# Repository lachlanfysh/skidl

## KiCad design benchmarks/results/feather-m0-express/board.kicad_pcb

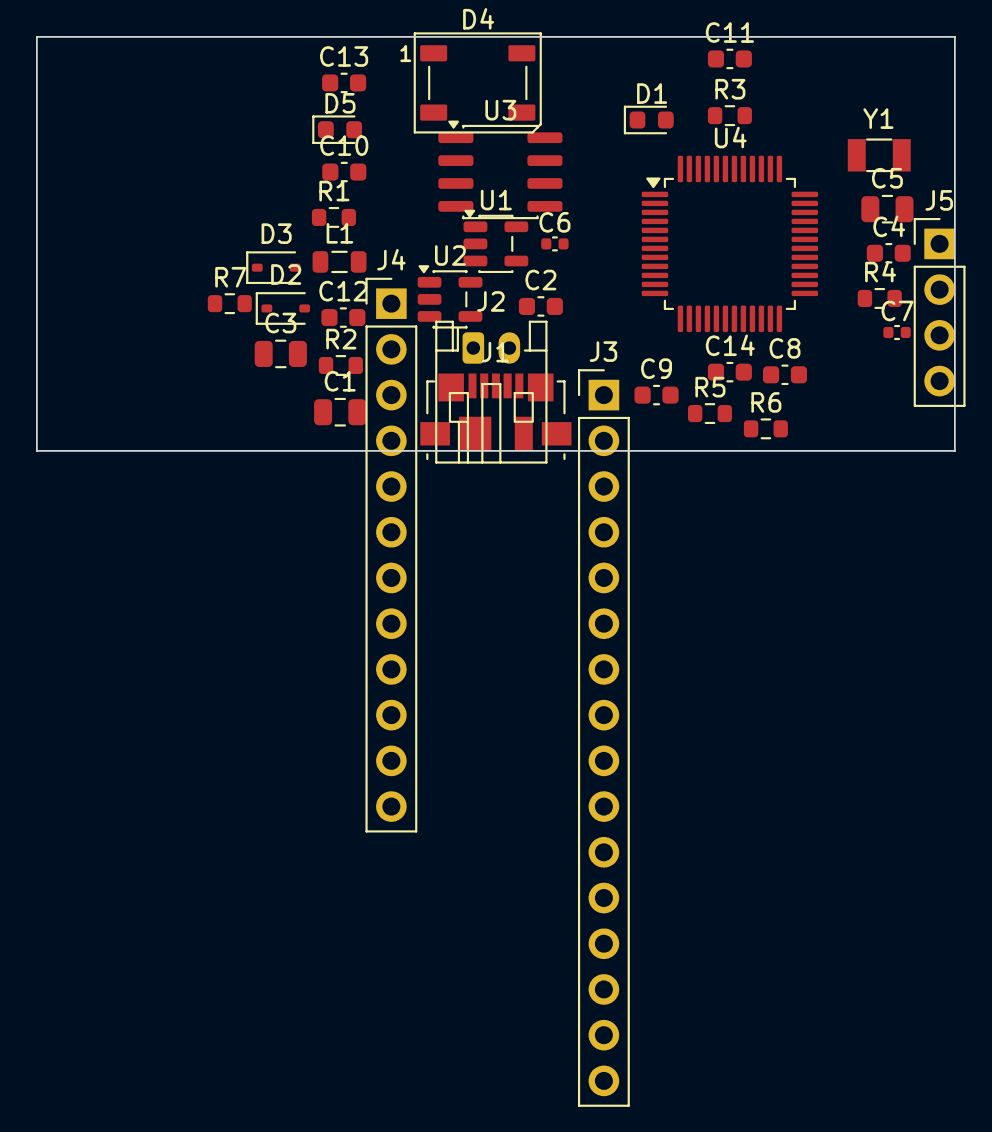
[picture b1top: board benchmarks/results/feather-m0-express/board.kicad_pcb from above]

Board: 2 copper layers, 51.0 x 23.0 mm, 37 parts (0 on the bottom side), 40 nets, no tracks yet.

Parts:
C1, C3, C5: 10uF; C_0805_2012Metric
C2, C4, C8, C9, C10, C12, C13, C14: 100nF; C_0603_1608Metric
C6, C7: 12pF; C_0402_1005Metric
C11: 1uF; C_0603_1608Metric
D1: Orange; LED_0603_1608Metric
D2, D3: MBR0520; D_SOD-323
D4: WS2812B; LED_WS2812B_PLCC4_5.0x5.0mm_P3.2mm
D5: Red; LED_0603_1608Metric
J1: USB_Micro_B; USB_Micro-B_Molex_47346-0001
J2: JST_PH_2; JST_PH_S2B-PH-K_1x02_P2.00mm_Horizontal
J3: Feather_Left; PinHeader_1x16_P2.54mm_Vertical
J4: Feather_Right; PinHeader_1x12_P2.54mm_Vertical
J5: SWD; PinHeader_1x04_P2.54mm_Vertical
L1: 600R@100MHz; L_0805_2012Metric
R1: 2K; R_0603_1608Metric
R2, R7: 1K; R_0603_1608Metric
R3, R4: 100K; R_0603_1608Metric
R5: 10K; R_0603_1608Metric
R6: SW_RST; R_0603_1608Metric
U1: MCP73831; SOT-23-5
U2: AP2112K-3.3; SOT-23-5
U3: GD25Q16C; SOIC-8_3.9x4.9mm_P1.27mm
U4: ATSAMD21G18A; TQFP-48_7x7mm_P0.5mm
Y1: 32.768kHz; Crystal_SMD_3215-2Pin_3.2x1.5mm

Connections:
+3V3: C4.1, C5.1, C9.1, C10.1, C12.1, C13.1, C14.1, D4.1, J3.2, J3.3, J5.1, R5.1, U2.5, U3.3, U3.7, U3.8, U4.6, U4.17, U4.36, U4.44
BAT_DIV: R3.2, R4.1, U4.12
FLASH_CS: U3.1, U4.22
GND: C1.2, C2.2, C3.2, C4.2, C5.2, C6.2, C7.2, C8.2, C9.2, C10.2, C11.2, C12.2, C13.2, C14.2, D4.3, D5.1, J1.5, J1.6, J2.2, J3.4, J5.4, R1.2, R4.2, R6.2, U1.2, U2.2, U3.4, U4.5, U4.18, U4.35, U4.42
HL_0: J3.5, U4.3
HL_1: J3.6, U4.4
HL_2: J3.7, U4.7
HL_3: J3.8, U4.8
HL_4: J3.9, U4.9
HL_5: J3.10, U4.10
HR_0: J4.4, R7.1, U4.26
HR_1: J4.5, U4.28
HR_2: J4.6, U4.25
HR_3: J4.7, U4.27
HR_4: J4.8, U4.29
HR_5: J4.9, U4.24
HR_6: J4.10, U4.23
HR_7: J3.14, U4.15
HR_8: J3.15, U4.16
MISO: J3.13, U3.2, U4.21
MOSI: J3.12, U3.5, U4.19
unnamed: R1.1, U1.5
unnamed: D1.2, R2.2
unnamed: D1.1, U1.1
unnamed: D5.2, R7.2
NEOPIXEL: D4.4, J3.16, U4.11
SCK: J3.11, U3.6, U4.20
SCL: J4.12, U4.32
SDA: J4.11, U4.31
SWCLK: J5.3, U4.45
SWDIO: J5.2, U4.46
USB_DM: J1.2, U4.33
USB_DP: J1.3, U4.34
VBAT: D3.2, J2.1, J4.1, R3.1, U1.3
VBUS: C1.1, C2.1, D2.2, J1.1, J4.3, L1.1, L1.2, R2.1, U1.4
VCC: C3.1, D2.1, D3.1, U2.1, U2.3
VDDCORE: C11.1, U4.43
XIN: C6.1, U4.1, Y1.1
XOUT: C7.1, U4.2, Y1.2
~RESET: C8.1, J3.1, R5.2, R6.1, U4.40

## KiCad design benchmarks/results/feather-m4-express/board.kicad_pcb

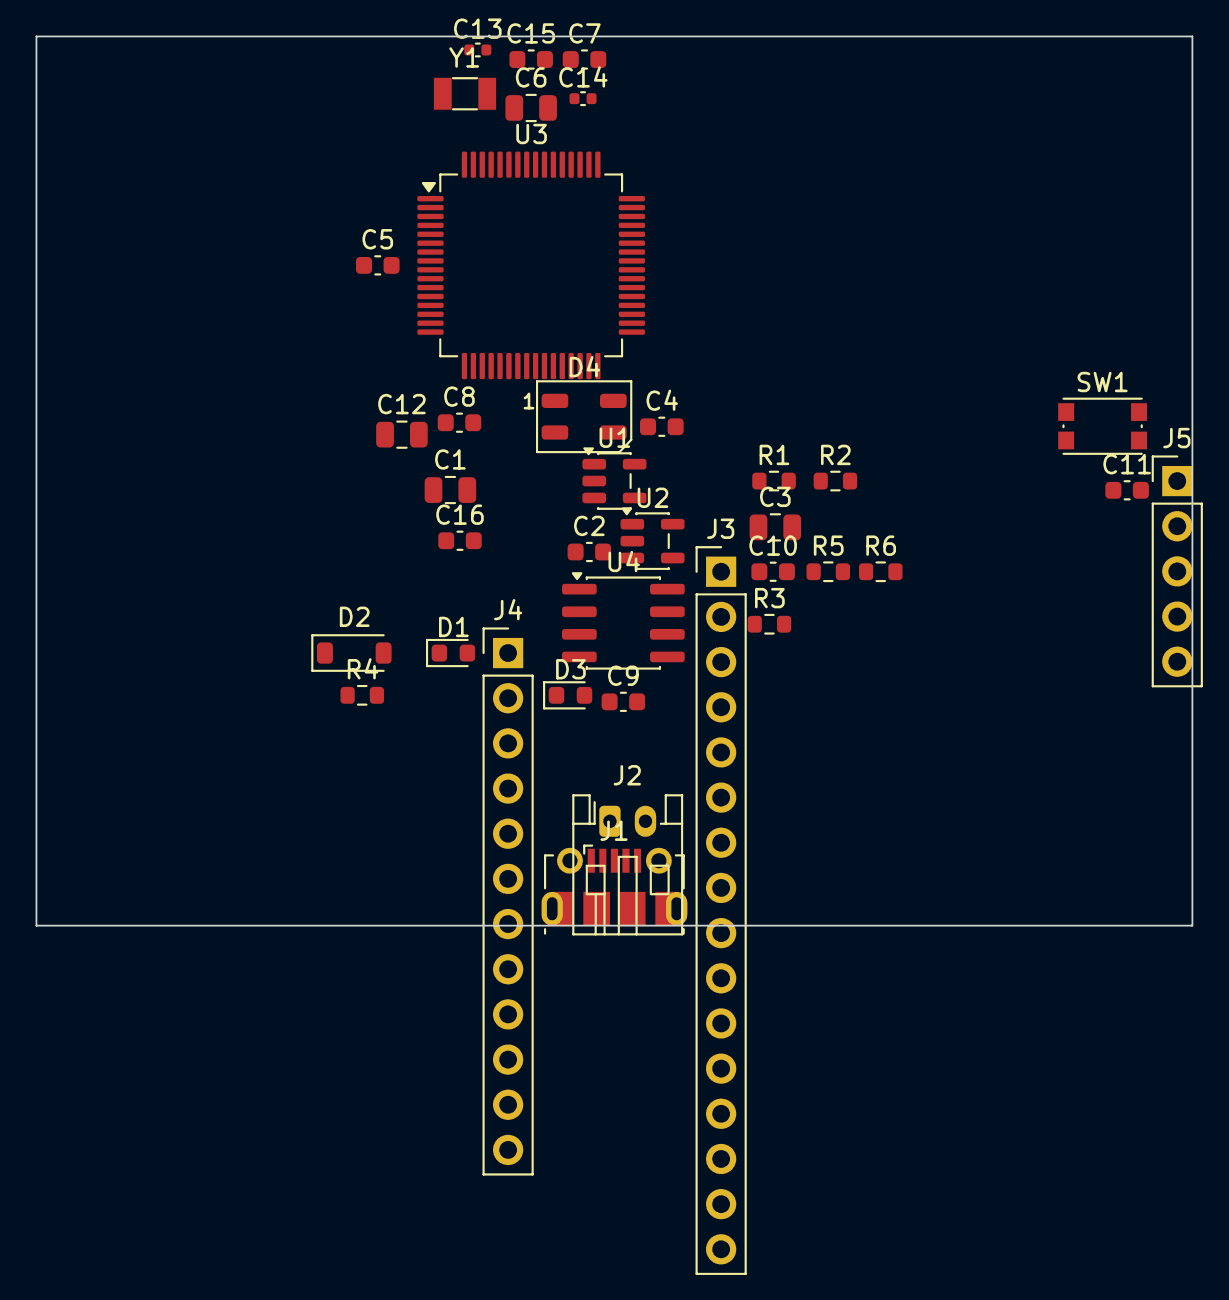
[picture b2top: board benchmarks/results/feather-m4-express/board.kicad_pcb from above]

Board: 2 copper layers, 65.0 x 50.0 mm, 37 parts (0 on the bottom side), 39 nets, no tracks yet.

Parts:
C1, C3, C6, C12: 10uF; C_0805_2012Metric
C2, C4, C5, C7, C8, C9, C10, C11, C15, C16: 100nF; C_0603_1608Metric
C13, C14: 12pF; C_0402_1005Metric
D1: Orange; LED_0603_1608Metric
D2: MBR120; D_SOD-123
D3: Red; LED_0603_1608Metric
D4: NeoPixel; LED_WS2812B-Mini_PLCC4_3.5x3.5mm
J1: USB_Micro-B; USB_Micro-B_Molex-105017-0001
J2: BATT; JST_PH_S2B-PH-K_1x02_P2.00mm_Horizontal
J3: HEADER_L; PinHeader_1x16_P2.54mm_Vertical
J4: HEADER_R; PinHeader_1x12_P2.54mm_Vertical
J5: SWD; PinHeader_1x05_P2.54mm_Vertical
R1: 2K; R_0603_1608Metric
R2, R4: 1K; R_0603_1608Metric
R3: 10K; R_0603_1608Metric
R5, R6: 4.7K; R_0603_1608Metric
SW1: RESET; SW_Push_1P1T_NO_CK_KMR2
U1: MCP73831; SOT-23-5
U2: AP2112K-3.3; SOT-23-5
U3: ATSAMD51J19A; TQFP-64_10x10mm_P0.5mm
U4: GD25Q16; SOIC-8_3.9x4.9mm_P1.27mm
Y1: 32.768kHz; Crystal_SMD_3215-2Pin_3.2x1.5mm

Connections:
+3V3: C5.1, C6.1, C8.1, C9.1, C10.1, C11.1, C12.1, C15.1, C16.1, D4.3, J3.2, J5.1, R3.1, R5.1, R6.1, U2.5, U3.8, U3.21, U3.34, U3.48, U3.56, U4.3, U4.7, U4.8
A0: J3.5, U3.3
A1: J3.6, U3.14
A2: J3.7, U3.11
A3: J3.8, U3.12
A4: J3.9, U3.13
A5: J3.10, U3.15
CHG_STAT: R2.1, U1.1
D4: J4.9, U3.31
D5: J3.13, U3.32
D6: J3.14, U3.37
D9: J3.15, J4.8, U3.38
D10: J3.16, J4.7, U3.41
D11: J4.6, U3.42
D12: J4.5, U3.4
D13: J4.4, R4.1, U3.35
FLASH_CS: U3.24, U4.1
GND: C1.2, C2.2, C3.2, C4.2, C5.2, C6.2, C7.2, C8.2, C9.2, C10.2, C11.2, C12.2, C13.2, C14.2, C15.2, C16.2, D3.1, D4.1, J1.5, J1.6, J2.2, J3.4, J5.2, R1.2, SW1.2, U1.2, U2.2, U3.7, U3.22, U3.33, U3.47, U3.54, U4.4
unnamed: R1.1, U1.5
unnamed: D1.1, R2.2
unnamed: D3.2, R4.2
NEOPIXEL: D4.2, U3.49
RESET_N: J3.1, J5.5, R3.2, SW1.1, U3.52
RX: J4.10, U3.40
SCL: J3.12, R6.2, U3.44
SDA: J3.11, R5.2, U3.43
SPI_MISO: J4.12, U3.18, U4.2
SPI_MOSI: U3.17, U4.5
SPI_SCK: U3.23, U4.6
SWDCLK: J5.4, U3.57
SWDIO: J5.3, U3.58
TX: J4.11, U3.39
USB_DM: J1.2, U3.45
USB_DP: J1.3, U3.46
VBAT: C3.1, C4.1, D2.1, J2.1, J4.1, U1.3, U2.1, U2.3
VBUS: C1.1, C2.1, D1.2, D2.2, J1.1, J4.3, U1.4
VDDCORE: C7.1, U3.53
XIN32: C13.1, U3.1, Y1.1
XOUT32: C14.1, U3.2, Y1.2

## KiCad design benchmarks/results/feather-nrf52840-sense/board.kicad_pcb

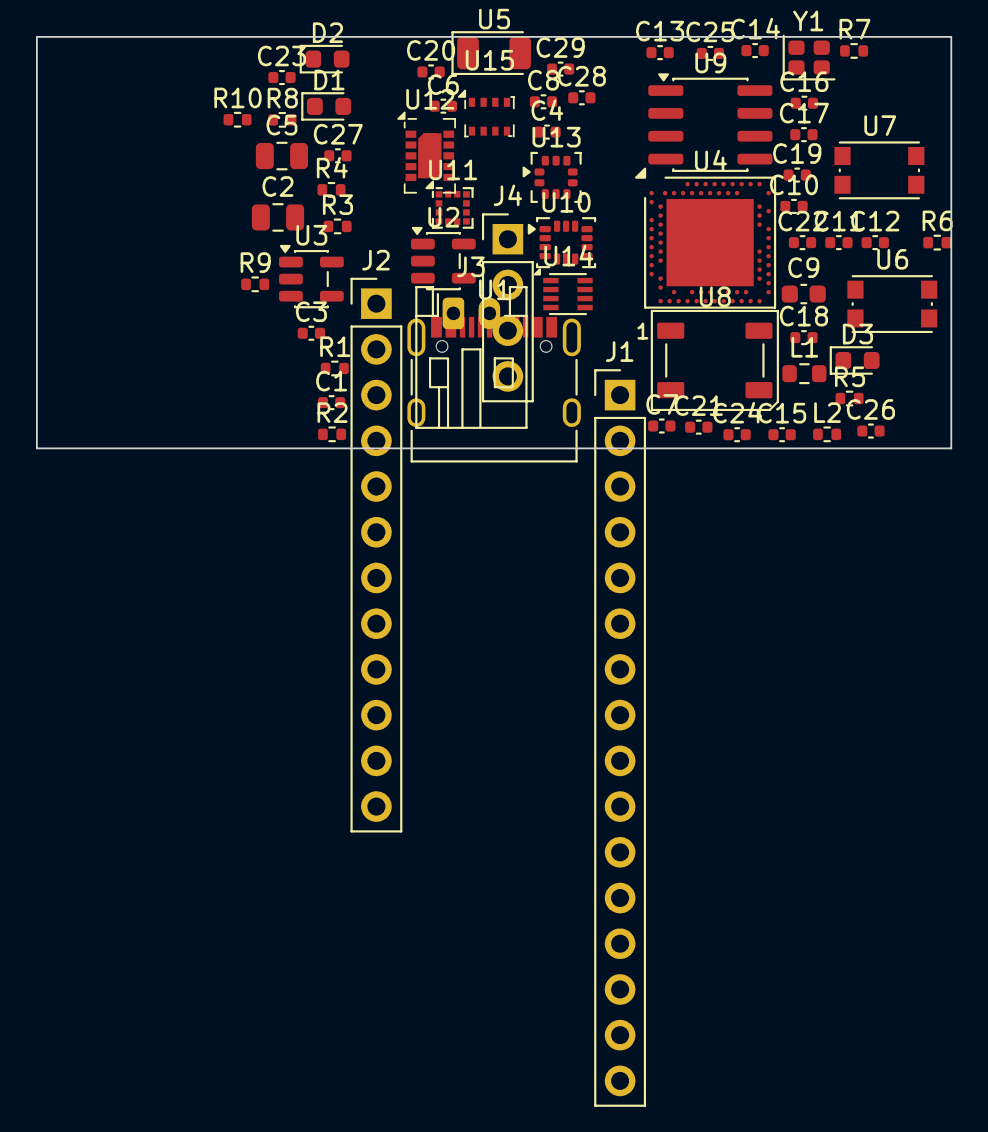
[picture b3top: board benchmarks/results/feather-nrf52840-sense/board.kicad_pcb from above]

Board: 2 copper layers, 50.8 x 22.9 mm, 64 parts (0 on the bottom side), 19 nets, no tracks yet.

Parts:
C1, C3, C4, C6, C7, C8, C10, C11, C12, C13, C14, C15, C20, C21, C22, C23, C24, C25, C27, C28, C29: 100nF; C_0402_1005Metric
C2, C5: 10uF; C_0805_2012Metric
C9: 4.7uF; C_0603_1608Metric
C16, C17: 12pF; C_0402_1005Metric
C18: 0.8pF; C_0402_1005Metric
C19: 1.0pF; C_0402_1005Metric
C26: 1uF; C_0402_1005Metric
D1: ORANGE; LED_0603_1608Metric
D2: RED; LED_0603_1608Metric
D3: BLUE; LED_0603_1608Metric
J1: Conn_01x16; PinHeader_1x16_P2.54mm_Vertical
J2: Conn_01x12; PinHeader_1x12_P2.54mm_Vertical
J3: Conn_01x02; JST_PH_S2B-PH-K_1x02_P2.00mm_Horizontal
J4: Conn_01x04; PinHeader_1x04_P2.54mm_Vertical
L1: 10uH; R_0603_1608Metric
L2: 3.3nH; R_0402_1005Metric
R1, R2: 5.1K; R_0402_1005Metric
R3: 2K; R_0402_1005Metric
R4, R6, R7: 1K; R_0402_1005Metric
R5: 10K; R_0402_1005Metric
R8, R9: 4.7K; R_0402_1005Metric
R10: 68R; R_0402_1005Metric
U1: USB_C_Receptacle; USB_C_Receptacle_XKB_U262-16XN-4BVC11
U2: MCP73831; SOT-23-5
U3: AP2112K-3.3; SOT-23-5
U4: nRF52840; Nordic_AQFN-73-1EP_7x7mm_P0.5mm
U5: ANT_2.4GHz; Johanson_2450AT18x100_2400-2500Mhz
U6: SW_RST; SW_Push_1P1T_NO_CK_KMR2
U7: SW_USR; SW_Push_1P1T_NO_CK_KMR2
U8: WS2812B; LED_WS2812B_PLCC4_5.0x5.0mm_P3.2mm
U9: GD25Q16; SOIC-8_3.9x4.9mm_P1.27mm
U10: LSM6DS33; LGA-14_3x2.5mm_P0.5mm_LayoutBorder3x4y
U11: LIS3MDL; LGA-12_2x2mm_P0.5mm
U12: APDS9960; AMS_LGA-10-1EP_2.7x4mm_P0.6mm
U13: MP34DT01; ST_HLGA-10_2.5x2.5mm_P0.6mm_LayoutBorder3x2y
U14: SHT30; DFN-8_2x2mm_P0.5mm
U15: BMP280; Bosch_LGA-8_2x2.5mm_P0.65mm_ClockwisePinNumbering
Y1: 32MHz; Crystal_SMD_2016-4Pin_2.0x1.6mm

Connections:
+3V3: C4.1, C5.1, C6.1, C7.1, C8.1, C9.1, C20.1, C21.1, C22.1, C24.1, C25.1, C26.1, C27.1, C28.1, C29.1, J1.2, J4.1, L1.2, R5.1, R8.1, R9.1, U3.5, U8.1, U9.8, U10.5, U10.8, U10.12, U11.4, U11.5, U11.10, U12.4, U12.5, U12.10, U13.5, U14.5, U14.6, U15.2, U15.6, U15.8
ANT_RF: C19.1, L2.2, U5.1
GND: C1.2, C2.2, C3.2, C4.2, C5.2, C6.2, C7.2, C8.2, C9.2, C10.2, C11.2, C12.2, C13.2, C14.2, C15.2, C16.2, C17.2, C18.2, C19.2, C20.2, C21.2, C22.2, C23.2, C24.2, C25.2, C26.2, C27.2, C28.2, C29.2, D1.2, D2.2, D3.2, J1.4, J3.2, J4.4, R1.2, R2.2, R3.2, R10.2, U2.2, U3.2, U4.EP, U5.2, U6.2, U7.2, U8.3, U9.4, U10.1, U10.6, U10.7, U11.2, U11.9, U11.11, U11.12, U12.2, U12.6, U12.11, U13.2, U13.4, U13.9, U13.10, U14.2, U14.8, U15.1, U15.5, U15.7
unnamed: R3.1, U2.5
unnamed: R4.1, U2.1
unnamed: D1.1, R4.2
unnamed: C16.1, Y1.1
unnamed: C17.1, Y1.2
unnamed: C18.1, L2.1
unnamed: R5.2, U6.1
unnamed: D2.1, R6.2
unnamed: D3.1, R7.2
unnamed: U4.P23, U9.1
unnamed: C23.1, U11.3
unnamed: R10.1, U12.3
SCL: J2.12, R9.2, U10.13, U11.1, U12.7, U14.4, U15.4
SDA: J2.11, R8.2, U10.14, U11.8, U12.1, U14.1, U15.3
VBAT: C2.1, C3.1, J2.1, J3.1, U2.3, U3.1, U3.3
VBUS: C1.1, J2.3, U2.4

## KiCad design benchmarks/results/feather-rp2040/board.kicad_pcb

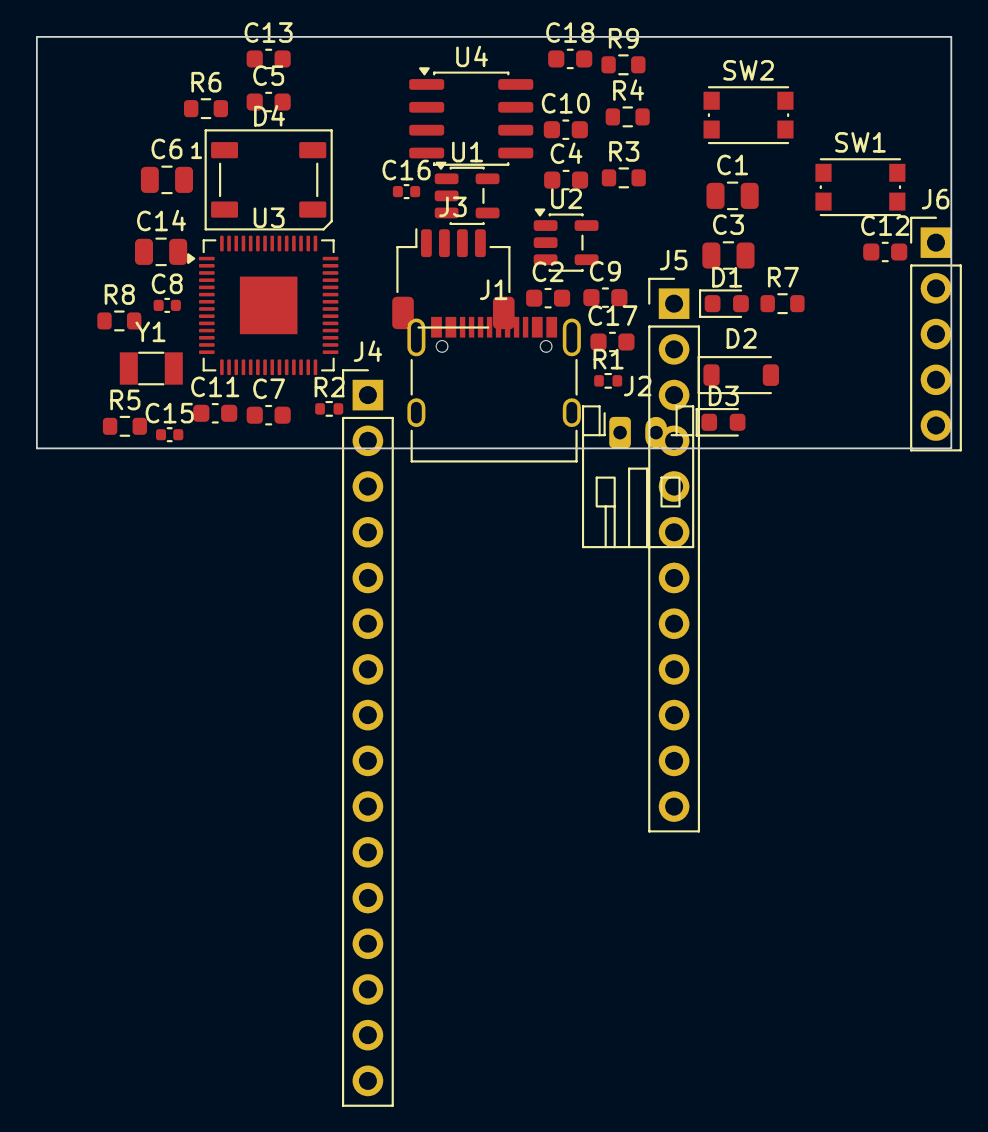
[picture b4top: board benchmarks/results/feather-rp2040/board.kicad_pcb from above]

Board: 2 copper layers, 50.8 x 22.9 mm, 44 parts (0 on the bottom side), 45 nets, no tracks yet.

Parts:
C1, C3, C6, C14: 10uF; C_0805_2012Metric
C2, C4, C5, C7, C9, C10, C11, C12, C13, C17, C18: 100nF; C_0603_1608Metric
C8: 1uF; C_0402_1005Metric
C15, C16: 15pF; C_0402_1005Metric
D1: Orange; LED_0603_1608Metric
D2: MBR120; D_SOD-123
D3: Red; LED_0603_1608Metric
D4: NeoPixel; LED_WS2812B_PLCC4_5.0x5.0mm_P3.2mm
J1: USB-C; USB_C_Receptacle_XKB_U262-16XN-4BVC11
J2: BATT; JST_PH_S2B-PH-K_1x02_P2.00mm_Horizontal
J3: STEMMA_QT; JST_SH_SM04B-SRSS-TB_1x04-1MP_P1.00mm_Horizontal
J4: HEADER_L; PinHeader_1x16_P2.54mm_Vertical
J5: HEADER_R; PinHeader_1x12_P2.54mm_Vertical
J6: SWD; PinHeader_1x05_P2.54mm_Vertical
R1, R2: 5.1K; R_0402_1005Metric
R3: 2K; R_0603_1608Metric
R4, R7: 1K; R_0603_1608Metric
R5, R6: 10K; R_0603_1608Metric
R8, R9: 4.7K; R_0603_1608Metric
SW1: RESET; SW_Push_1P1T_NO_CK_KMR2
SW2: BOOTSEL; SW_Push_1P1T_NO_CK_KMR2
U1: MCP73831; SOT-23-5
U2: AP2112K-3.3; SOT-23-5
U3: RP2040; QFN-56-1EP_7x7mm_P0.4mm_EP3.2x3.2mm
U4: GD25Q64; SOIC-8_3.9x4.9mm_P1.27mm
Y1: 12MHz; Crystal_SMD_3215-2Pin_3.2x1.5mm

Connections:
+3V3: C5.1, C6.1, C9.1, C10.1, C11.1, C12.1, C13.1, C14.1, C17.1, C18.1, D4.3, J3.2, J4.2, J6.1, R5.1, R6.1, R8.1, R9.1, U2.5, U3.1, U3.10, U3.22, U3.33, U3.42, U3.43, U3.44, U3.48, U3.49, U4.8
A0: J4.5, U3.38
A1: J4.6, U3.39
A2: J4.7, U3.40
A3: J4.8, U3.41
BOOTSEL: R6.2, SW2.1
CHG_STAT: R4.1, U1.1
D4: J5.9, U3.6
D5: J4.13, U3.7
D6: J4.14, U3.8
D9: J4.15, J5.8, U3.9
D10: J4.16, J5.7, U3.11
D11: J5.6, U3.12
D12: J5.5, U3.13
D13: J5.4, R7.1, U3.14
D24: J4.9, U3.36
D25: J4.10, U3.37
DVDD: C7.1, C8.1, U3.23, U3.45, U3.50
GND: C1.2, C2.2, C3.2, C4.2, C5.2, C6.2, C7.2, C8.2, C9.2, C10.2, C11.2, C12.2, C13.2, C14.2, C15.2, C16.2, C17.2, C18.2, D3.1, D4.1, J1.A1, J1.A12, J1.B1, J1.B12, J1.S1, J2.2, J3.1, J4.4, J6.2, R1.2, R2.2, R3.2, SW1.2, SW2.2, U1.2, U2.2, U3.19, U3.57, U4.4
unnamed: J1.A5, R1.1
unnamed: J1.B5, R2.1
unnamed: R3.1, U1.5
unnamed: D1.1, R4.2
unnamed: D3.2, R7.2
NEOPIXEL: D4.2, U3.27
QSPI_SCLK: U3.52, U4.6
QSPI_SD0: U3.53, U4.5
QSPI_SD1: U3.55, U4.2
QSPI_SD2: U3.54, U4.3
QSPI_SD3: U3.51, U4.7
QSPI_SS: U3.56, U4.1
RESET_N: J4.1, J6.5, R5.2, SW1.1, U3.26
RX: J5.10, U3.3
SCL: J3.4, J4.12, R9.2, U3.5
SDA: J3.3, J4.11, R8.2, U3.4
SPI_MISO: J5.12, U3.31
SWDCLK: J6.4, U3.24
SWDIO: J6.3, U3.25
TX: J5.11, U3.2
USB_DM: J1.A7, J1.B7, U3.46
USB_DP: J1.A6, J1.B6, U3.47
VBAT: C3.1, C4.1, D2.1, J2.1, J5.1, U1.3, U2.1, U2.3
VBUS: C1.1, C2.1, D1.2, D2.2, J1.A4, J1.A9, J1.B4, J1.B9, J5.3, U1.4
XIN: C15.1, U3.20, Y1.1
XOUT: C16.1, U3.21, Y1.2

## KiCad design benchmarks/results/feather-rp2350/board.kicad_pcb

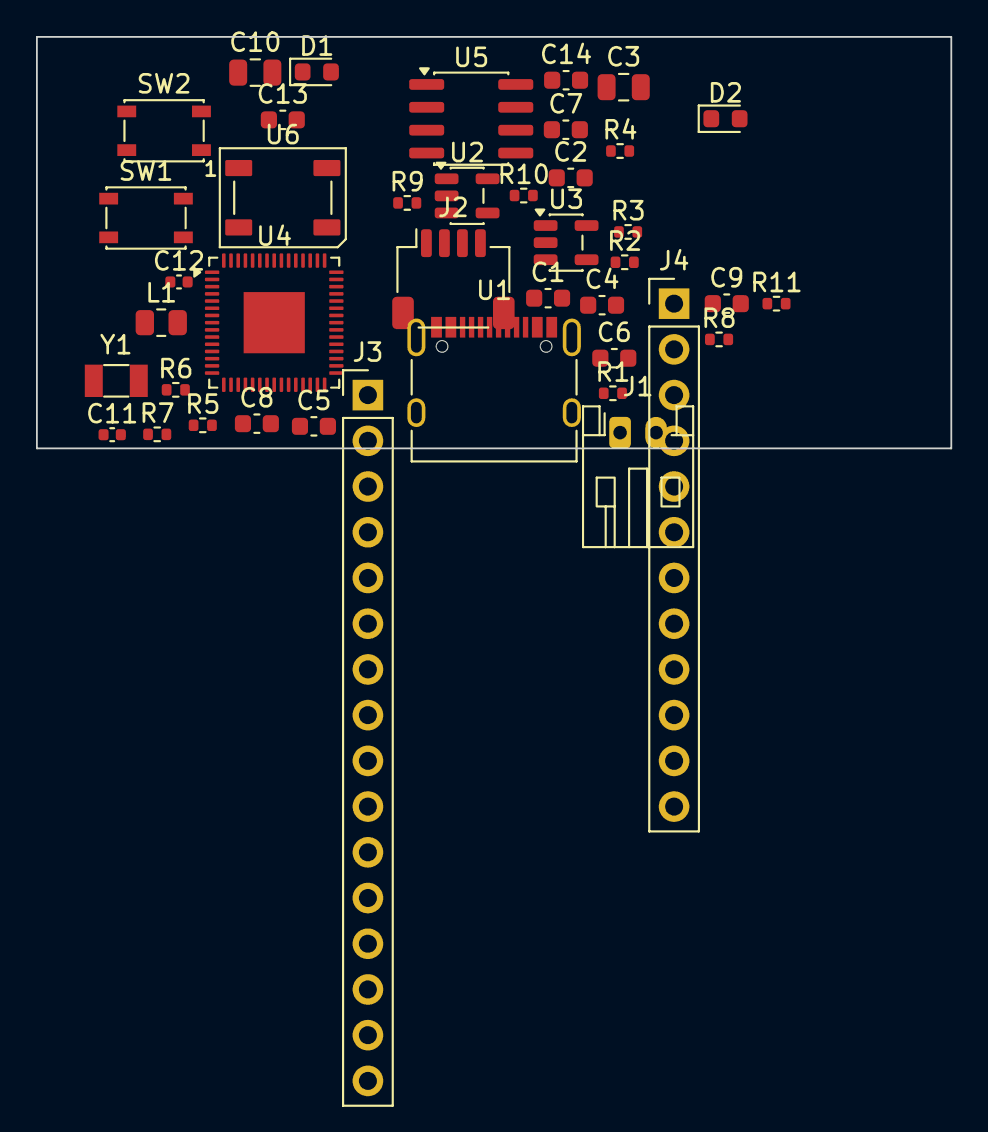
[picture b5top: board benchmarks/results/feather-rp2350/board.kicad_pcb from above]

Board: 2 copper layers, 50.8 x 22.9 mm, 41 parts (0 on the bottom side), 46 nets, no tracks yet.

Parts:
C1, C2, C4, C5, C6, C7, C8, C9, C13, C14: 100nF; C_0603_1608Metric
C3, C10: 10uF; C_0805_2012Metric
C11, C12: 20pF; C_0402_1005Metric
D1: ORANGE; LED_0603_1608Metric
D2: RED; LED_0603_1608Metric
J1: Conn_01x02; JST_PH_S2B-PH-K_1x02_P2.00mm_Horizontal
J2: Conn_01x04; JST_SH_SM04B-SRSS-TB_1x04-1MP_P1.00mm_Horizontal
J3: Conn_01x16; PinHeader_1x16_P2.54mm_Vertical
J4: Conn_01x12; PinHeader_1x12_P2.54mm_Vertical
L1: 3.3uH; R_0805_2012Metric
R1, R2: 5.1K; R_0402_1005Metric
R3: 2K; R_0402_1005Metric
R4: 1K; R_0402_1005Metric
R5: 100K; R_0402_1005Metric
R6: 220K; R_0402_1005Metric
R7, R10: 10K; R_0402_1005Metric
R8, R9: 4.7K; R_0402_1005Metric
R11: 330R; R_0402_1005Metric
SW1, SW2: SW_Push; SW_SPST_PTS810
U1: USB_C_16P; USB_C_Receptacle_XKB_U262-16XN-4BVC11
U2: AP2112K-3.3; SOT-23-5
U3: MCP73831; SOT-23-5
U4: RP2350A; QFN-60-1EP_7x7mm_P0.4mm_EP3.4x3.4mm
U5: W25Q64JV; SOIC-8_3.9x4.9mm_P1.27mm
U6: WS2812B; LED_WS2812B_PLCC4_5.0x5.0mm_P3.2mm
Y1: 12MHz; Crystal_SMD_3215-2Pin_3.2x1.5mm

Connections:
+3V3: C2.1, C3.1, C6.1, C7.1, C8.1, C9.1, C10.1, C13.1, C14.1, J2.2, J3.2, J4.1, L1.2, R5.1, R7.1, R8.1, R9.1, R10.1, U2.5, U4.1, U4.6, U4.11, U4.20, U4.23, U4.30, U4.38, U4.39, U4.44, U4.45, U4.46, U4.49, U4.53, U4.54, U5.8, U6.1
BOOTSEL: R10.2, SW2.1
CHG_STAT: R4.1, U3.1
GND: C1.2, C2.2, C3.2, C4.2, C5.2, C6.2, C7.2, C8.2, C9.2, C10.2, C11.2, C12.2, C13.2, C14.2, D1.2, D2.2, J1.2, J2.1, J3.16, J4.3, R1.2, R2.2, R3.2, R6.2, SW1.2, SW2.2, U1.A1, U1.A12, U1.B1, U1.B12, U1.S1, U2.2, U3.2, U4.47, U4.61, U5.4, U6.3
GPIO0: J3.15, U4.2
GPIO1: J3.14, U4.3
GPIO4: J4.12, U4.7
GPIO8: J3.10, U4.12
GPIO9: J3.9, U4.13
GPIO10: J3.8, U4.14
GPIO11: J3.7, U4.15
GPIO12: J3.6, U4.16
GPIO13: J3.5, U4.17
GPIO14: J3.4, U4.18
GPIO21: J4.9, U4.33
GPIO22: J3.13, U4.34
GPIO23: J3.12, U4.35
GPIO24: J3.11, U4.36
GPIO25: J4.8, R11.1, U4.37
GPIO26: J4.4, U4.40
GPIO27: J4.5, U4.41
GPIO28: J4.6, U4.42
GPIO29: J4.2, J4.7, U4.43
unnamed: R1.1, U1.A5
unnamed: R2.1, U1.B5
unnamed: R3.1, U3.5
unnamed: D1.1, R4.2
unnamed: D2.1, R11.2
NEOPIXEL: U4.27, U6.4
QSPI_CLK: U4.56, U5.6
QSPI_CS: U4.60, U5.1
QSPI_D0: U4.57, U5.5
QSPI_D1: U4.59, U5.2
QSPI_D2: U4.58, U5.3
QSPI_D3: U4.55, U5.7
RUN1: R7.2, U4.26
SCL: J2.4, J4.10, R9.2, U4.5
SDA: J2.3, J4.11, R8.2, U4.4
USB_DM: U1.A7, U1.B7, U4.51
USB_DP: U1.A6, U1.B6, U4.52
VBAT: C5.1, J1.1, J3.1, U3.3
VBUS: C1.1, C4.1, J3.3, U1.A4, U1.A9, U1.B4, U1.B9, U2.1, U2.3, U3.4
VREG_FB: R5.2, R6.1, U4.50
VREG_LX: L1.1, U4.48
XIN: C11.1, U4.21, Y1.1
XOUT: C12.1, U4.22, Y1.2

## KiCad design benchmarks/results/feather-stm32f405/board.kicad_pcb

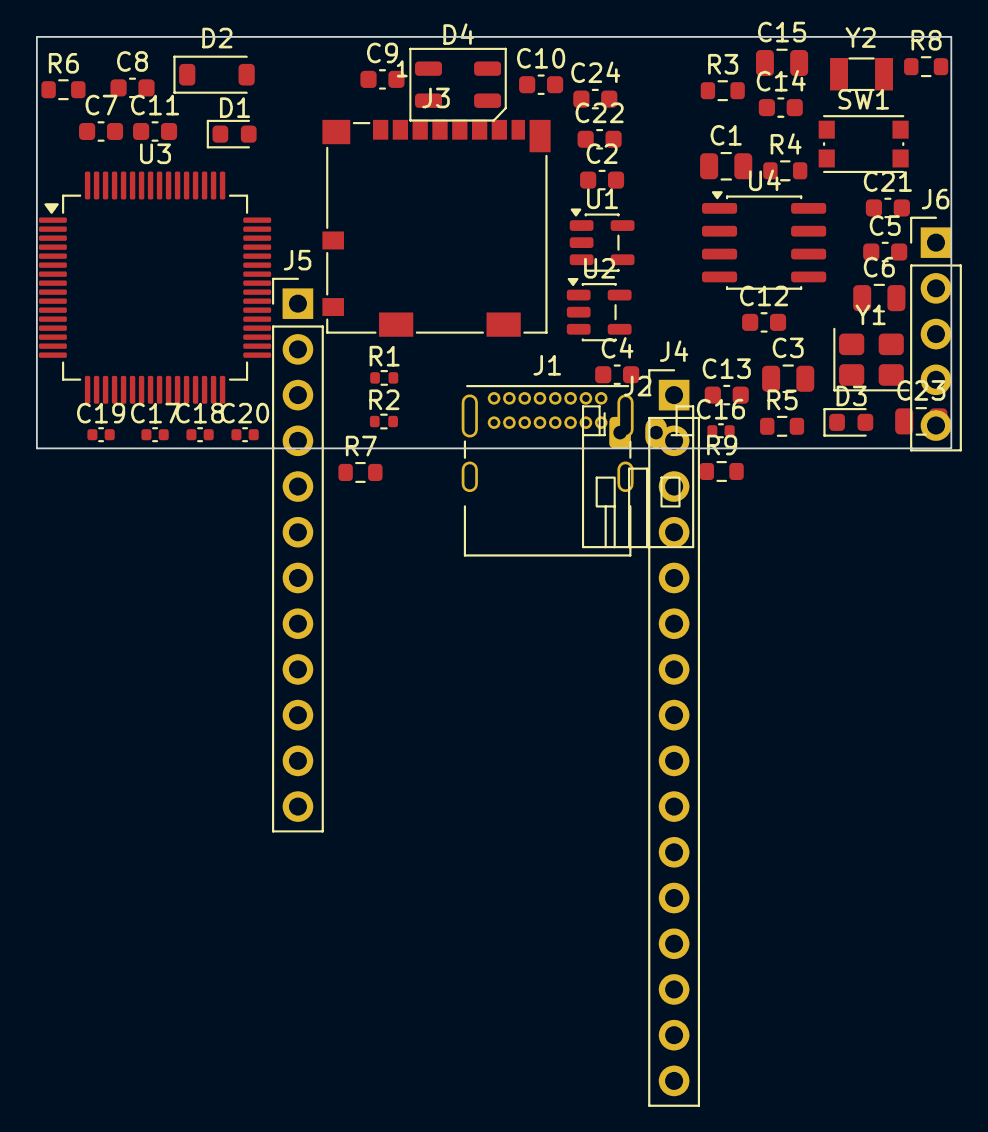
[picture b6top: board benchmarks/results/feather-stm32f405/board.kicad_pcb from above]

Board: 2 copper layers, 50.8 x 22.9 mm, 50 parts (0 on the bottom side), 49 nets, no tracks yet.

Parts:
C1, C3, C6, C15, C23: 10uF; C_0805_2012Metric
C2, C4, C5, C9, C10, C11, C12, C13, C21, C22, C24: 100nF; C_0603_1608Metric
C7, C8: 2.2uF; C_0603_1608Metric
C14: 1uF; C_0603_1608Metric
C16: 100nF; C_0402_1005Metric
C17, C18: 20pF; C_0402_1005Metric
C19, C20: 6.8pF; C_0402_1005Metric
D1: Orange; LED_0603_1608Metric
D2: MBR120; D_SOD-123
D3: Red; LED_0603_1608Metric
D4: NeoPixel; LED_WS2812B-Mini_PLCC4_3.5x3.5mm
J1: USB-C; USB_C_Receptacle_GCT_USB4085
J2: BATT; JST_PH_S2B-PH-K_1x02_P2.00mm_Horizontal
J3: MicroSD; microSD_HC_Molex_104031-0811
J4: HEADER_L; PinHeader_1x16_P2.54mm_Vertical
J5: HEADER_R; PinHeader_1x12_P2.54mm_Vertical
J6: SWD; PinHeader_1x05_P2.54mm_Vertical
R1, R2: 5.1K; R_0402_1005Metric
R3: 2K; R_0603_1608Metric
R4, R7: 1K; R_0603_1608Metric
R5, R6: 10K; R_0603_1608Metric
R8, R9: 4.7K; R_0603_1608Metric
SW1: RESET; SW_Push_1P1T_NO_CK_KMR2
U1: MCP73831; SOT-23-5
U2: AP2112K-3.3; SOT-23-5
U3: STM32F405RGT6; LQFP-64_10x10mm_P0.5mm
U4: GD25Q16; SOIC-8_3.9x4.9mm_P1.27mm
Y1: 8MHz; Crystal_SMD_3225-4Pin_3.2x2.5mm
Y2: 32.768kHz; Crystal_SMD_3215-2Pin_3.2x1.5mm

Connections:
+3V3: C5.1, C6.1, C9.1, C10.1, C11.1, C12.1, C13.1, C14.1, C15.1, C21.1, C22.1, C23.1, C24.1, D4.3, J3.4, J4.2, J6.1, R5.1, R8.1, R9.1, U2.5, U3.1, U3.13, U3.19, U3.32, U3.48, U3.64, U4.3, U4.7, U4.8
A0: J4.5, U3.14
A1: J4.6, U3.15
A2: J4.7, U3.16
A3: J4.8, U3.17
A4: J4.9, U3.20
A5: J4.10, U3.21
BOOT0: R6.1, U3.60
CC1: J1.A5, R1.1
CC2: J1.B5, R2.1
CHG_STAT: R4.1, U1.1
D4: J5.9, U3.27
D5: J4.13, U3.38
D6: J4.14, U3.37
D9: J4.15, J5.8, U3.61
D10: J4.16, J5.7, U3.62
D11: J5.6, U3.11
D12: J5.5, U3.10
D13: J5.4, R7.1, U3.9
FLASH_CS: U3.50, U4.1
GND: C1.2, C2.2, C3.2, C4.2, C5.2, C6.2, C7.2, C8.2, C9.2, C10.2, C11.2, C12.2, C13.2, C14.2, C15.2, C16.2, C17.2, C18.2, C19.2, C20.2, C21.2, C22.2, C23.2, C24.2, D3.1, D4.1, J1.A1, J1.A12, J1.B1, J1.B12, J1.S1, J2.2, J3.6, J3.9, J4.4, J6.2, R1.2, R2.2, R3.2, R6.2, SW1.2, U1.2, U2.2, U3.12, U3.18, U3.63, U4.4
HSE_IN: C17.1, U3.5, Y1.1
HSE_OUT: C18.1, U3.6, Y1.2
LSE_IN: C19.1, U3.3, Y2.1
LSE_OUT: C20.1, U3.4, Y2.2
unnamed: R3.1, U1.5
unnamed: D1.1, R4.2
unnamed: D3.2, R7.2
NEOPIXEL: D4.2, U3.8
RESET_N: C16.1, J4.1, J6.5, R5.2, SW1.1, U3.7
RX: J5.10, U3.30
SCL: J4.12, R9.2, U3.58
SDA: J4.11, R8.2, U3.59
SD_CS: J3.2, U3.33
SD_MISO: J3.7, U3.35
SD_MOSI: J3.3, U3.36
SD_SCK: J3.5, U3.34
SPI_MISO: J5.12, U3.56, U4.2
SPI_MOSI: U3.57, U4.5
SPI_SCK: U3.55, U4.6
SWDCLK: J6.4, U3.49
SWDIO: J6.3, U3.46
TX: J5.11, U3.29
USB_DM: J1.A7, J1.B7, U3.44
USB_DP: J1.A6, J1.B6, U3.45
VBAT: C3.1, C4.1, D2.1, J2.1, J5.1, U1.3, U2.1, U2.3
VBUS: C1.1, C2.1, D1.2, D2.2, J1.A4, J1.A9, J1.B4, J1.B9, J5.3, U1.4
VCAP1: C7.1, U3.31
VCAP2: C8.1, U3.47

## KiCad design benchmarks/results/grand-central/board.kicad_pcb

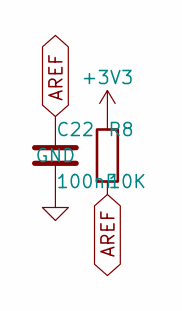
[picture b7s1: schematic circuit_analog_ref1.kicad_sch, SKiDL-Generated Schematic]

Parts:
C22: 100nF; C_0603_1608Metric
R8: 10K; R_0603_1608Metric

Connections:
+3V3: R8.1; also elsewhere on the board
AREF: C22.1, R8.2; also elsewhere on the board
GND: C22.2; also elsewhere on the board

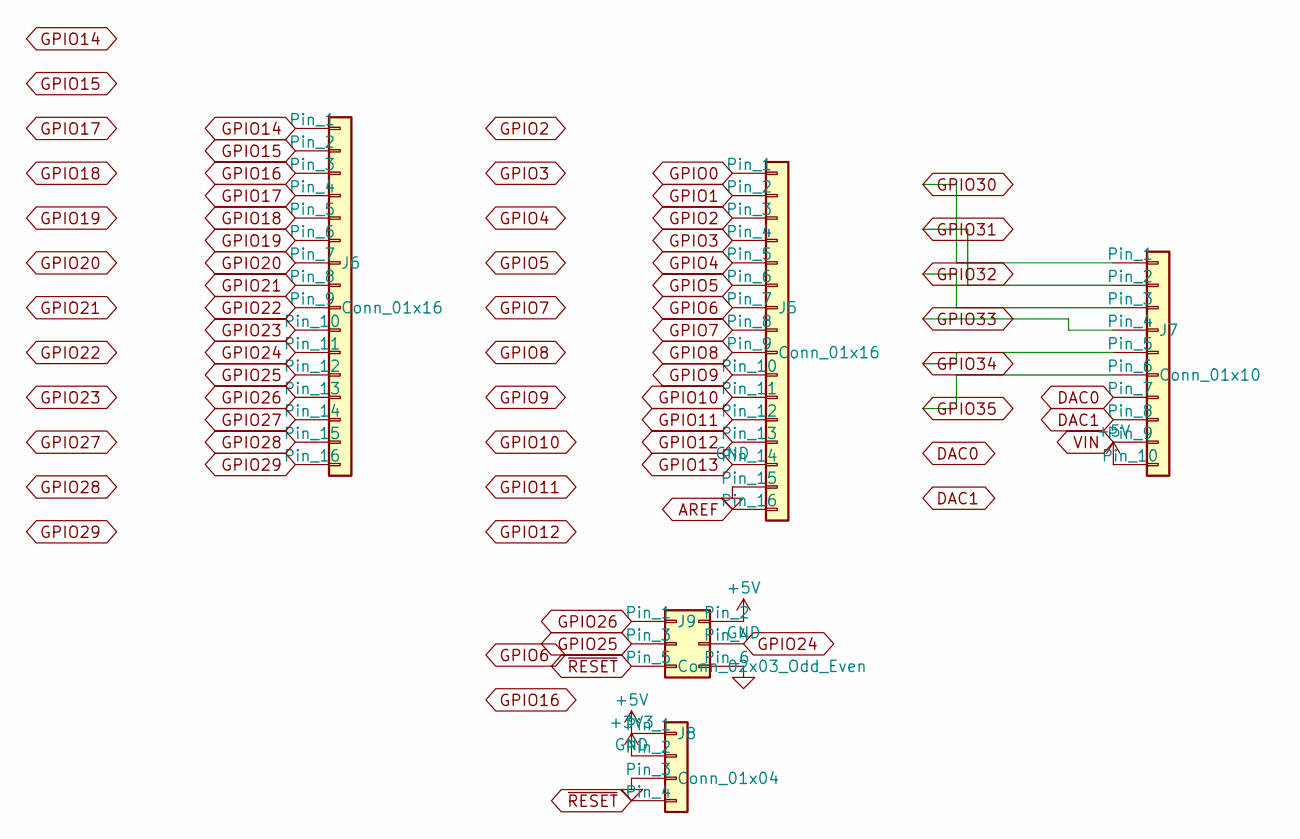
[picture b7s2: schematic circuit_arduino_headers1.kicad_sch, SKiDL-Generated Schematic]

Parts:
J5, J6: Conn_01x16; PinHeader_1x16_P2.54mm_Vertical
J7: Conn_01x10; PinHeader_1x10_P2.54mm_Vertical
J8: Conn_01x04; PinHeader_1x04_P2.54mm_Vertical
J9: Conn_02x03_Odd_Even; PinHeader_2x03_P2.54mm_Vertical

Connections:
+3V3: J8.2; also elsewhere on the board
+5V: J7.10, J8.1, J9.2; also elsewhere on the board
AREF: J5.16; also elsewhere on the board
DAC0: J7.7; also elsewhere on the board
DAC1: J7.8; also elsewhere on the board
GND: J5.15, J8.3, J9.6; also elsewhere on the board
GPIO0: J5.1; also elsewhere on the board
GPIO1: J5.2; also elsewhere on the board
GPIO2: J5.3; also elsewhere on the board
GPIO3: J5.4; also elsewhere on the board
GPIO4: J5.5; also elsewhere on the board
GPIO5: J5.6; also elsewhere on the board
GPIO6: J5.7; also elsewhere on the board
GPIO7: J5.8; also elsewhere on the board
GPIO8: J5.9; also elsewhere on the board
GPIO9: J5.10; also elsewhere on the board
GPIO10: J5.11; also elsewhere on the board
GPIO11: J5.12; also elsewhere on the board
GPIO12: J5.13; also elsewhere on the board
GPIO13: J5.14; also elsewhere on the board
GPIO14: J6.1; also elsewhere on the board
GPIO15: J6.2; also elsewhere on the board
GPIO16: J6.3; also elsewhere on the board
GPIO17: J6.4; also elsewhere on the board
GPIO18: J6.5; also elsewhere on the board
GPIO19: J6.6; also elsewhere on the board
GPIO20: J6.7; also elsewhere on the board
GPIO21: J6.8; also elsewhere on the board
GPIO22: J6.9; also elsewhere on the board
GPIO23: J6.10; also elsewhere on the board
GPIO24: J6.11, J9.4; also elsewhere on the board
GPIO25: J6.12, J9.3; also elsewhere on the board
GPIO26: J6.13, J9.1; also elsewhere on the board
GPIO27: J6.14; also elsewhere on the board
GPIO28: J6.15; also elsewhere on the board
GPIO29: J6.16; also elsewhere on the board
GPIO30: J7.1
GPIO31: J7.2
GPIO32: J7.3
GPIO33: J7.4
GPIO34: J7.5
GPIO35: J7.6
VIN: J7.9; also elsewhere on the board
~RESET: J8.4, J9.5; also elsewhere on the board

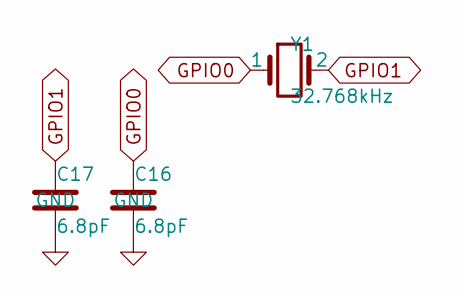
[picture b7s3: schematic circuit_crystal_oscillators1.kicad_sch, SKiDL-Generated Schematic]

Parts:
C16, C17: 6.8pF; C_0603_1608Metric
Y1: 32.768kHz; Crystal_SMD_2012-2Pin_2.0x1.2mm

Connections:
GND: C16.2, C17.2; also elsewhere on the board
GPIO0: C16.1, Y1.1; also elsewhere on the board
GPIO1: C17.1, Y1.2; also elsewhere on the board

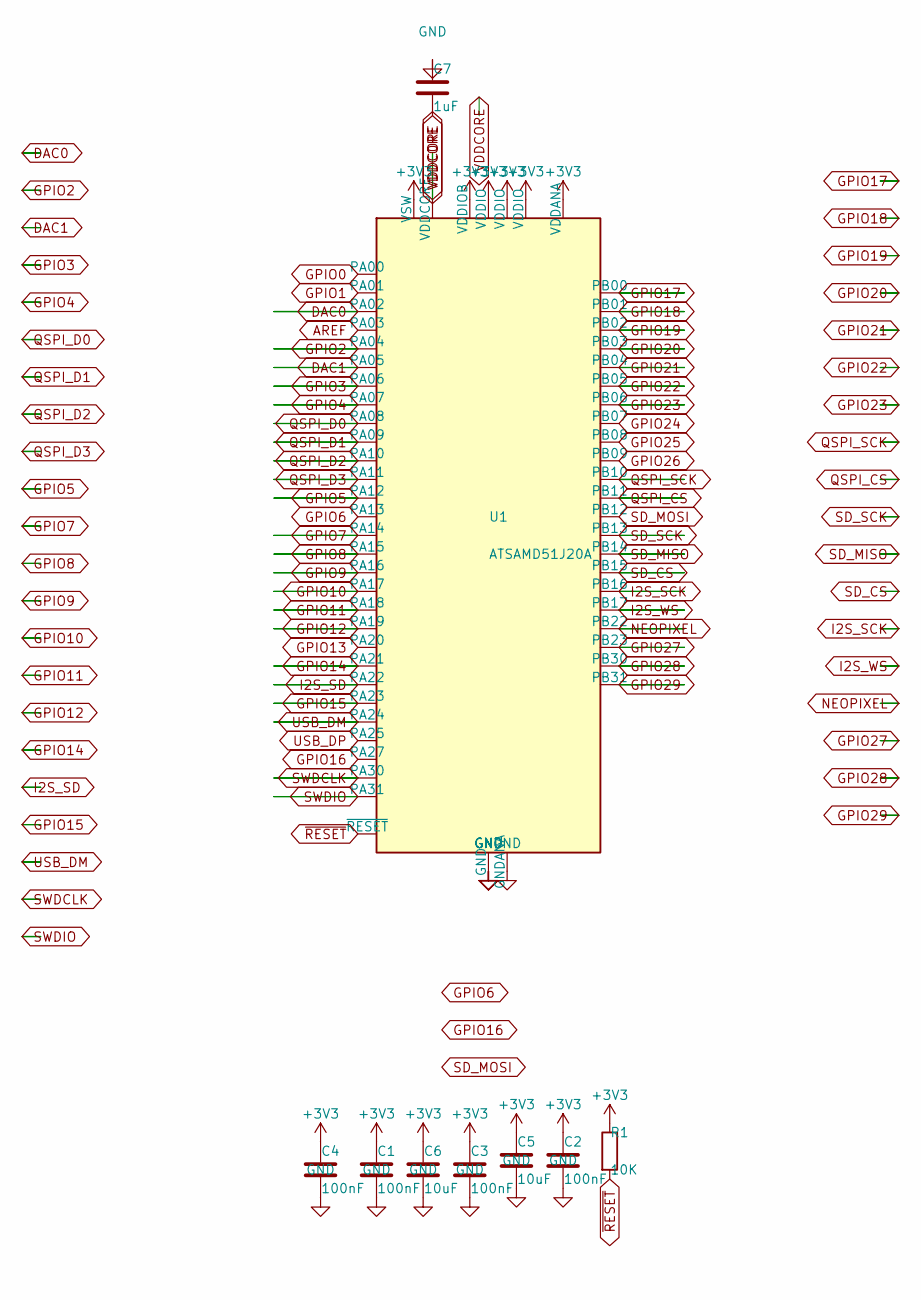
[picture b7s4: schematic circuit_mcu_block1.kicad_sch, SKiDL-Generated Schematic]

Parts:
C1, C2, C3, C4: 100nF; C_0603_1608Metric
C5, C6: 10uF; C_0805_2012Metric
C7: 1uF; C_0603_1608Metric
R1: 10K; R_0603_1608Metric
U1: ATSAMD51J20A; LQFP-64_10x10mm_P0.5mm

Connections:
+3V3: C1.1, C2.1, C3.1, C4.1, C5.1, C6.1, R1.1, U1.8 (VDDANA), U1.21 (VDDIOB), U1.34 (VDDIO), U1.48 (VDDIO), U1.55 (VSW), U1.56 (VDDIO); also elsewhere on the board
AREF: U1.4 (PA03); also elsewhere on the board
DAC0: U1.3 (PA02); also elsewhere on the board
DAC1: U1.14 (PA05); also elsewhere on the board
GND: C1.2, C2.2, C3.2, C4.2, C5.2, C6.2, C7.2, U1.7 (GNDANA), U1.22 (GND), U1.33 (GND), U1.47 (GND), U1.54 (GND); also elsewhere on the board
GPIO0: U1.1 (PA00); also elsewhere on the board
GPIO1: U1.2 (PA01); also elsewhere on the board
GPIO2: U1.13 (PA04); also elsewhere on the board
GPIO3: U1.15 (PA06); also elsewhere on the board
GPIO4: U1.16 (PA07); also elsewhere on the board
GPIO5: U1.29 (PA12); also elsewhere on the board
GPIO6: U1.30 (PA13); also elsewhere on the board
GPIO7: U1.31 (PA14); also elsewhere on the board
GPIO8: U1.32 (PA15); also elsewhere on the board
GPIO9: U1.35 (PA16); also elsewhere on the board
GPIO10: U1.36 (PA17); also elsewhere on the board
GPIO11: U1.37 (PA18); also elsewhere on the board
GPIO12: U1.38 (PA19); also elsewhere on the board
GPIO13: U1.41 (PA20); also elsewhere on the board
GPIO14: U1.42 (PA21); also elsewhere on the board
GPIO15: U1.44 (PA23); also elsewhere on the board
GPIO16: U1.51 (PA27); also elsewhere on the board
GPIO17: U1.61 (PB00); also elsewhere on the board
GPIO18: U1.62 (PB01); also elsewhere on the board
GPIO19: U1.63 (PB02); also elsewhere on the board
GPIO20: U1.64 (PB03); also elsewhere on the board
GPIO21: U1.5 (PB04); also elsewhere on the board
GPIO22: U1.6 (PB05); also elsewhere on the board
GPIO23: U1.9 (PB06); also elsewhere on the board
GPIO24: U1.10 (PB07); also elsewhere on the board
GPIO25: U1.11 (PB08); also elsewhere on the board
GPIO26: U1.12 (PB09); also elsewhere on the board
GPIO27: U1.50 (PB23); also elsewhere on the board
GPIO28: U1.59 (PB30); also elsewhere on the board
GPIO29: U1.60 (PB31); also elsewhere on the board
I2S_SCK: U1.39 (PB16)
I2S_SD: U1.43 (PA22)
I2S_WS: U1.40 (PB17)
NEOPIXEL: U1.49 (PB22); also elsewhere on the board
QSPI_CS: U1.24 (PB11); also elsewhere on the board
QSPI_D0: U1.17 (PA08); also elsewhere on the board
QSPI_D1: U1.18 (PA09); also elsewhere on the board
QSPI_D2: U1.19 (PA10); also elsewhere on the board
QSPI_D3: U1.20 (PA11); also elsewhere on the board
QSPI_SCK: U1.23 (PB10); also elsewhere on the board
SD_CS: U1.28 (PB15); also elsewhere on the board
SD_MISO: U1.27 (PB14); also elsewhere on the board
SD_MOSI: U1.25 (PB12); also elsewhere on the board
SD_SCK: U1.26 (PB13); also elsewhere on the board
SWDCLK: U1.57 (PA30); also elsewhere on the board
SWDIO: U1.58 (PA31); also elsewhere on the board
USB_DM: U1.45 (PA24); also elsewhere on the board
USB_DP: U1.46 (PA25); also elsewhere on the board
VDDCORE: C7.1, U1.53 (VDDCORE)
~RESET: R1.2, U1.52 (~RESET); also elsewhere on the board

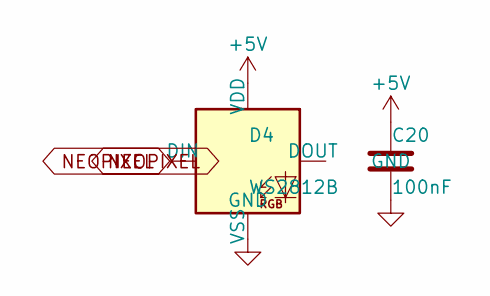
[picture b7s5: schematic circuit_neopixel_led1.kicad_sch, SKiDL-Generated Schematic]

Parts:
C20: 100nF; C_0603_1608Metric
D4: WS2812B; LED_WS2812B_PLCC4_5.0x5.0mm_P3.2mm

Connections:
+5V: C20.1, D4.1 (VDD); also elsewhere on the board
GND: C20.2, D4.3 (VSS); also elsewhere on the board
NEOPIXEL: D4.4 (DIN); also elsewhere on the board
